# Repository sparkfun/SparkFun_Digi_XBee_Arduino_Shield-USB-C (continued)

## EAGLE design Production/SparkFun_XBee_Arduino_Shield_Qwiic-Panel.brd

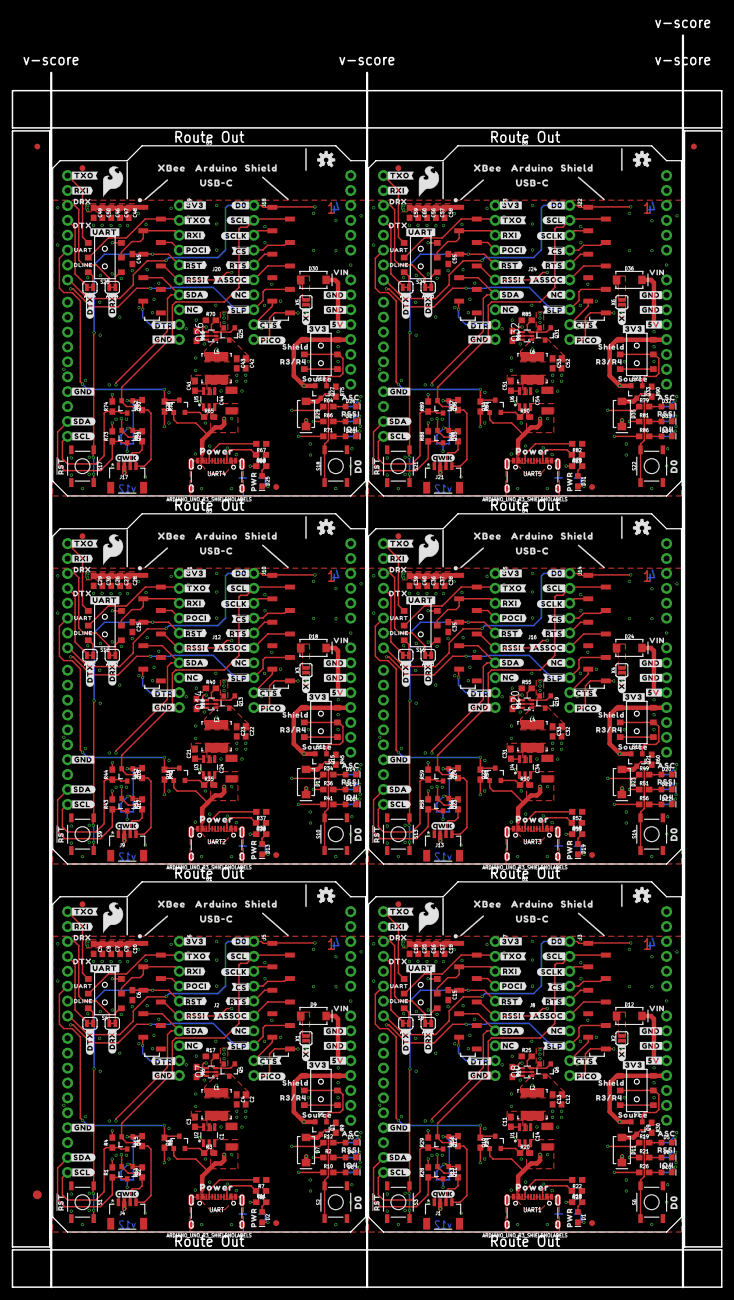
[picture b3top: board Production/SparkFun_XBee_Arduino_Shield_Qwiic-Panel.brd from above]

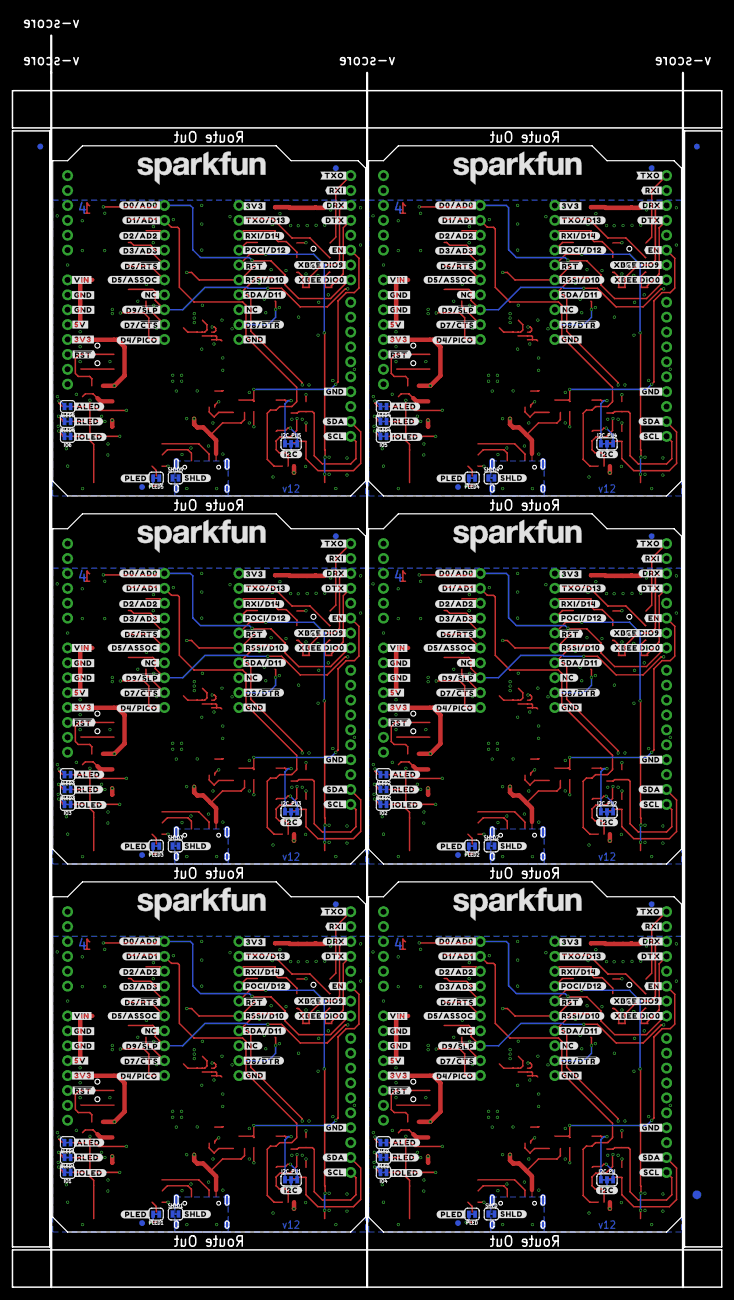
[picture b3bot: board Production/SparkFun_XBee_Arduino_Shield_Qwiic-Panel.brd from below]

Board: 4 copper layers, 120.8 x 217.2 mm, 972 parts (309 on the bottom side), 312 nets.

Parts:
ALED, ALED1, ALED2, ALED3, ALED4, ALED5: JUMPER-SMT_2_NC_TRACE_SILK; SMT-JUMPER_2_NC_TRACE_SILK
ARX, ARX1, ARX2, ARX3, ARX4, ARX5: JUMPER-SMT_2_NC_TRACE_SILK; SMT-JUMPER_2_NC_TRACE_SILK
ATX, ATX1, ATX2, ATX3, ATX4, ATX5: JUMPER-SMT_2_NC_TRACE_SILK; SMT-JUMPER_2_NC_TRACE_SILK
B1, B2, B3, B4, B5, B6: ARDUINO_UNO_R3_SHIELDNOLABELS; UNO_R3_SHIELD_NOLABELS
C1, C14, C24, C34, C44, C54: 10uF; 1210
C2, C4, C12, C13, C22, C23, C32, C33, C42, C43, C52, C53: 22uF; 0603
C3, C9, C11, C17, C21, C27, C31, C37, C41, C47, C51, C57: 0.1uF; 0603
C5, C19, C29, C39, C49, C59: 47pF; 0603
C6, C7, C15, C16, C25, C26, C35, C36, C45, C46, C55, C56: 10nF; 0603
C8, C20, C30, C40, C50, C60: 10pF; 0603
C10, C18, C28, C38, C48, C58: 10uF; 0603
D1, D2, D13, D19, D25, D31: RED; LED-0603
D3, D5, D14, D20, D26, D32: BLUE; LED-0603
D4, D8, D15, D21, D27, D33: Yellow; LED-0603
D6, D10, D16, D22, D28, D34: GREEN; LED-0603
D7, D9, D11, D12, D17, D18, D23, D24, D29, D30, D35, D36: 3A/40V/500mV; SMA-DIODE
E$1, E$2, E$3, E$4: FIDUCIAL-1X2
E$5, E$6: FIDUCIAL-1.5X3
FD1, FD2, FD3, FD4, FD5, FD6, FD7, FD8, FD9, FD10, FD11, FD12, FD13, FD14, FD15, FD16, FD17, FD18, FD19, FD20, FD21, FD22, FD23, FD24: FIDUCIAL1X2; FIDUCIAL-1X2
I2C_PU, I2C_PU1, I2C_PU2, I2C_PU3, I2C_PU4, I2C_PU5: JUMPER-SMT_3_2-NC_TRACE_SILK; SMT-JUMPER_3_2-NC_TRACE_SILK
IO1, IO2, IO3, IO4, IO5, IO6: JUMPER-SMT_2_NC_TRACE_SILK; SMT-JUMPER_2_NC_TRACE_SILK
J1, J4, J9, J13, J17, J21: QWIIC_RIGHT_ANGLE; JST04_1MM_RA
J2, J8, J12, J16, J20, J24: XBEE3-SMD
J3, J5, J6, J7, J10, J11, J14, J15, J18, J19, J22, J23: 1X10_NO_SILK
L1, L2, L3, L4, L5, L6: 3.9UH; INDUCTOR_3.9UH
LOGO1, LOGO6, LOGO9, LOGO12, LOGO15, LOGO18: SFE_LOGO_NAMEBLANK; BLANK
LOGO2, LOGO4, LOGO7, LOGO10, LOGO13, LOGO16: OSHW-LOGOS; OSHW-LOGO-S
LOGO3, LOGO5, LOGO8, LOGO11, LOGO14, LOGO17: QWIIC_LOGO_4MM; QWIIC_4MM
PLED, PLED1, PLED2, PLED3, PLED4, PLED5: JUMPER-SMT_2_NC_TRACE_SILK; SMT-JUMPER_2_NC_TRACE_SILK
Q1, Q2, Q4, Q10, Q11, Q12, Q16, Q17, Q18, Q22, Q23, Q24, Q28, Q29, Q30, Q34, Q35, Q36: 220mA/50V/3.5Ω; SOT23-3
Q3, Q9, Q15, Q21, Q27, Q33: 3.1A/30V/105mΩ; SOT23-3
Q5, Q6, Q13, Q19, Q25, Q31: 20V/4.2A/52mΩ/1.4W; SOT23-3
Q7, Q8, Q14, Q20, Q26, Q32: SOT363_PHILIPS
R1, R2, R4, R12, R13, R14, R15, R16, R19, R21, R28, R29, R31, R32, R34, R36, R43, R44, R46, R47, R49, R51, R58, R59, R61, R62, R64, R66, R73, R74, R76, R77, R79, R81, R88, R89: 2.2k; 0603
R3, R6, R9, R20, R24, R30, R35, R39, R45, R50, R54, R60, R65, R69, R75, R80, R84, R90: 100k; 0603
R5, R27, R42, R57, R72, R87: 10k; 0603
R7, R8, R22, R23, R37, R38, R52, R53, R67, R68, R82, R83: 5.1k; 0603
R10, R26, R41, R56, R71, R86: 330; 0603
R11, R18, R33, R48, R63, R78: 4.7k; 0603
R17, R25, R40, R55, R70, R85: 1M; 0603
RLED, RLED1, RLED2, RLED3, RLED4, RLED5: JUMPER-SMT_2_NC_TRACE_SILK; SMT-JUMPER_2_NC_TRACE_SILK
S1, S2, S3, S6, S9, S10, S13, S14, S17, S18, S21, S22: TACTILE_SWITCH_SMD_5.2MM
S4, S5, S7, S8, S11, S12, S15, S16, S19, S20, S23, S24: SWITCH_DPDT_SMD_AYZ0202
SHLD, SHLD1, SHLD2, SHLD3, SHLD4, SHLD5: JUMPER-SMT_2_NC_TRACE_SILK; SMT-JUMPER_2_NC_TRACE_SILK
U1, U2, U3, U4, U5, U6: AP63203; SOT23-6
U$1, U$146, U$242, U$338, U$434, U$530: RSSI31
U$2, U$147, U$243, U$339, U$435, U$531: PWR29
U$3, U$56, U$123, U$136, U$219, U$232, U$315, U$328, U$411, U$424, U$507, U$520: #SDA#10
U$4, U$130, U$226, U$322, U$418, U$514: #SHLD#36
U$5, U$9, U$131, U$135, U$227, U$231, U$323, U$327, U$419, U$423, U$515, U$519: #NC#1
U$6, U$103, U$199, U$295, U$391, U$487: #D3#AD3#23
U$7, U$10, U$132, U$133, U$228, U$229, U$324, U$325, U$420, U$421, U$516, U$517: #NC#3
U$8, U$155, U$251, U$347, U$443, U$539: ##DTR##27
U$11, U$101, U$197, U$293, U$389, U$485: #D1#AD1#8
U$12, U$156, U$252, U$348, U$444, U$540: ##CTS##28
U$13, U$109, U$205, U$301, U$397, U$493: #D8##DTR##27
U$14, U$110, U$206, U$302, U$398, U$494: #RSSI#D10#17
U$15, U$111, U$207, U$303, U$399, U$495: #SDA#D11#9
U$16, U$112, U$208, U$304, U$400, U$496: ##RST##15
U$17, U$113, U$209, U$305, U$401, U$497: #POCI#D12#24
U$18, U$114, U$210, U$306, U$402, U$498: #RXI#D14#15
U$19, U$102, U$198, U$294, U$390, U$486: #D2#AD2#19
U$20, U$104, U$200, U$296, U$392, U$488: #D6##RTS##25
U$21, U$32, U$118, U$139, U$214, U$235, U$310, U$331, U$406, U$427, U$502, U$523: #TXO#8
U$22, U$115, U$211, U$307, U$403, U$499: #TXO#D13#13
U$23, U$162, U$258, U$354, U$450, U$546: VIN5
U$24, U$137, U$233, U$329, U$425, U$521: #SCL#7
U$25, U$29, U$41, U$50, U$53, U$63, U$76, U$82, U$134, U$138, U$142, U$148, U$157, U$165, U$166, U$170, U$230, U$234, U$238, U$244, U$253, U$261, U$262, U$266, U$326, U$330, U$334, U$340, U$349, U$357, U$358, U$362, U$422, U$426, U$430, U$436, U$445, U$453, U$454, U$458, U$518, U$522, U$526, U$532, U$541, U$549, U$550, U$554: #GND#0
U$26, U$97, U$193, U$289, U$385, U$481: #I2C#33
U$27, U$33, U$119, U$140, U$215, U$236, U$311, U$332, U$407, U$428, U$503, U$524: #RXI#7
U$28, U$177, U$273, U$369, U$465, U$561: DRX52
U$30, U$99, U$195, U$291, U$387, U$483: #RST#30
U$31, U$163, U$259, U$355, U$451, U$547: #PICO#27
U$34, U$178, U$274, U$370, U$466, U$562: DTX53
U$35, U$105, U$201, U$297, U$393, U$489: #D5#ASSOC#25
U$36, U$106, U$202, U$298, U$394, U$490: #D9##SLP##28
U$37, U$107, U$203, U$299, U$395, U$491: #D7##CTS##26
U$38, U$108, U$204, U$300, U$396, U$492: #D4#PICO#25
U$39, U$66, U$154, U$167, U$250, U$263, U$346, U$359, U$442, U$455, U$538, U$551: #5V#5
U$40, U$98, U$194, U$290, U$386, U$482: D03
U$42, U$179, U$275, U$371, U$467, U$563: DLINE45
U$43, U$164, U$260, U$356, U$452, U$548: #X1#10
U$44, U$47, U$77, U$84, U$141, U$149, U$158, U$172, U$237, U$245, U$254, U$268, U$333, U$341, U$350, U$364, U$429, U$437, U$446, U$460, U$525, U$533, U$542, U$556: #3V3#1
U$45, U$120, U$216, U$312, U$408, U$504: #POCI#32
U$46, U$190, U$286, U$382, U$478, U$574: SHIELD55
U$48, U$180, U$276, U$372, U$468, U$564: UART44
U$49, U$116, U$212, U$308, U$404, U$500: #ALED#21
U$51, U$117, U$213, U$309, U$405, U$501: #RLED#22
U$52, U$159, U$255, U$351, U$447, U$543: #PLED#20
U$54, U$87, U$121, U$173, U$217, U$269, U$313, U$365, U$409, U$461, U$505, U$557: ##RST##13
U$55, U$122, U$218, U$314, U$410, U$506: #RSSI#16
U$57, U$124, U$220, U$316, U$412, U$508: #ASSOC#28
U$58, U$125, U$221, U$317, U$413, U$509: ##RTS##14
U$59, U$126, U$222, U$318, U$414, U$510: ##CS##26
U$60, U$127, U$223, U$319, U$415, U$511: #SCLK#33
U$61, U$100, U$196, U$292, U$388, U$484: SFE_LOGO_FLAME_.2
U$62, U$143, U$239, U$335, U$431, U$527: SFE_LOGO_NAME_.2
U$64, U$128, U$224, U$320, U$416, U$512: #SCL#9
U$65, U$129, U$225, U$321, U$417, U$513: #D0#3
U$67, U$168, U$264, U$360, U$456, U$552: #SDA#9
U$68, U$144, U$240, U$336, U$432, U$528: ##SLP##28
U$69, U$191, U$287, U$383, U$479, U$575: R3#R455
U$70, U$169, U$265, U$361, U$457, U$553: #SCL#13
U$71, U$86, U$181, U$185, U$277, U$281, U$373, U$377, U$469, U$473, U$565, U$569: #DRX#56
U$72, U$89, U$182, U$186, U$278, U$282, U$374, U$378, U$470, U$474, U$566, U$570: #DTX#57
U$73, U$183, U$279, U$375, U$471, U$567: #TXO#61
U$74, U$145, U$241, U$337, U$433, U$529: ASC32
U$75, U$176, U$272, U$368, U$464, U$560: POWER49
U$78, U$150, U$246, U$342, U$438, U$534: #D0#AD0#18
U$79, U$151, U$247, U$343, U$439, U$535: ARDUINO1345
U$80, U$152, U$248, U$344, U$440, U$536: XBEE340
U$81, U$153, U$249, U$345, U$441, U$537: SHIELD1346
U$83, U$171, U$267, U$363, U$459, U$555: #EN#15
U$85, U$184, U$280, U$376, U$472, U$568: #RXI#60
U$88, U$174, U$270, U$366, U$462, U$558: #VIN#4
U$90, U$187, U$283, U$379, U$475, U$571: #XBEE_DIO0#62
U$91, U$175, U$271, U$367, U$463, U$559: #UART#4048234
U$92, U$188, U$284, U$380, U$476, U$572: #XBEE_DIO9#62
U$93, U$160, U$256, U$352, U$448, U$544: #IOLED#5
U$94, U$161, U$257, U$353, U$449, U$545: IO49
U$95, U$189, U$285, U$381, U$477, U$573: SOURCE54
U$96, U$192, U$288, U$384, U$480, U$576: USB#C58
UART, UART1, UART2, UART3, UART4, UART5: USB Female Type C Connector; USB-C-16P-4LAYER-ISOLATED
X1, X2, X3, X4, X5, X6: JUMPER-SMT_2_NO_SILK; SMT-JUMPER_2_NO_SILK

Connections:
3.3V: C5.1, C7.1, C8.1, C9.1, C10.1, D7.C, I2C_PU.2, J2.1, J4.2, J6.1, Q5.2, Q7.4, R11.1
3.3V1: C16.1, C17.1, C18.1, C19.1, C20.1, D11.C, I2C_PU1.2, J1.2, J7.1, J8.1, Q6.2, Q8.4, R18.1
3.3V2: C26.1, C27.1, C28.1, C29.1, C30.1, D17.C, I2C_PU2.2, J9.2, J11.1, J12.1, Q13.2, Q14.4, R33.1
3.3V3: C36.1, C37.1, C38.1, C39.1, C40.1, D23.C, I2C_PU3.2, J13.2, J15.1, J16.1, Q19.2, Q20.4, R48.1
3.3V4: C46.1, C47.1, C48.1, C49.1, C50.1, D29.C, I2C_PU4.2, J17.2, J19.1, J20.1, Q25.2, Q26.4, R63.1
3.3V5: C56.1, C57.1, C58.1, C59.1, C60.1, D35.C, I2C_PU5.2, J21.2, J23.1, J24.1, Q31.2, Q32.4, R78.1
3.3V_R1: B2.3.3V, Q9.2, R27.2, R28.2, R29.2, S7.3, S7.6
3.3V_R2: B3.3.3V, Q15.2, R42.2, R43.2, R44.2, S11.3, S11.6
3.3V_R3: B1.3.3V, Q3.2, R1.2, R4.2, R5.2, S5.3, S5.6
3.3V_R4: B4.3.3V, Q21.2, R57.2, R58.2, R59.2, S15.3, S15.6
3.3V_R5: B5.3.3V, Q27.2, R72.2, R73.2, R74.2, S19.3, S19.6
3.3V_R6: B6.3.3V, Q33.2, R87.2, R88.2, R89.2, S23.3, S23.6
3.3V_VREG: C2.1, C4.1, L1.P$2, Q5.3, Q7.1, U2.1
3.3V_VREG1: C12.1, C13.1, L2.P$2, Q6.3, Q8.1, U1.1
3.3V_VREG2: C22.1, C23.1, L3.P$2, Q13.3, Q14.1, U3.1
3.3V_VREG3: C32.1, C33.1, L4.P$2, Q19.3, Q20.1, U4.1
3.3V_VREG4: C42.1, C43.1, L5.P$2, Q25.3, Q26.1, U5.1
3.3V_VREG5: C52.1, C53.1, L6.P$2, Q31.3, Q32.1, U6.1
5V: B1.5V, D9.C
5V1: B2.5V, D12.C
5V2: B3.5V, D18.C
5V3: B4.5V, D24.C
5V4: B5.5V, D30.C
5V5: B6.5V, D36.C
!RESET!: C6.1, J2.5, J6.5, S1.1, S1.2
!RESET!1: C15.1, J7.5, J8.5, S3.1, S3.2
!RESET!2: C25.1, J11.5, J12.5, S9.1, S9.2
!RESET!3: C35.1, J15.5, J16.5, S13.1, S13.2
!RESET!4: C45.1, J19.5, J20.5, S17.1, S17.2
!RESET!5: C55.1, J23.5, J24.5, S21.1, S21.2
D0: B1.D7, J2.20, J5.1, S2.1, S2.2
D1: B2.D7, J3.1, J8.20, S6.1, S6.2
D1/SCL: J2.19, J4.4, J5.2, Q4.2, R15.1
D1/SCL1: J1.4, J3.2, J8.19, Q12.2, R16.1
D1/SCL2: J9.4, J10.2, J12.19, Q18.2, R32.1
D1/SCL3: J13.4, J14.2, J16.19, Q24.2, R47.1
D1/SCL4: J17.4, J18.2, J20.19, Q30.2, R62.1
D1/SCL5: J21.4, J22.2, J24.19, Q36.2, R77.1
D2: B3.D7, J10.1, J12.20, S10.1, S10.2
D2/SPI_CLK: J2.18, J5.3
D2/SPI_CLK1: J3.3, J8.18
D2/SPI_CLK2: J10.3, J12.18
D2/SPI_CLK3: J14.3, J16.18
D2/SPI_CLK4: J18.3, J20.18
D2/SPI_CLK5: J22.3, J24.18
D3: B4.D7, J14.1, J16.20, S14.1, S14.2
D3/SPI_!CS!: J2.17, J5.4
D3/SPI_!CS!1: J3.4, J8.17
D3/SPI_!CS!2: J10.4, J12.17
D3/SPI_!CS!3: J14.4, J16.17
D3/SPI_!CS!4: J18.4, J20.17
D3/SPI_!CS!5: J22.4, J24.17
D4: B5.D7, J18.1, J20.20, S18.1, S18.2
D4/SPI_PICO: J2.11, J5.10, R10.1
D4/SPI_PICO1: J3.10, J8.11, R26.1
D4/SPI_PICO2: J10.10, J12.11, R41.1
D4/SPI_PICO3: J14.10, J16.11, R56.1
D4/SPI_PICO4: J18.10, J20.11, R71.1
D4/SPI_PICO5: J22.10, J24.11, R86.1
D5: B6.D7, J22.1, J24.20, S22.1, S22.2
D5/ASSOCIATE: J2.15, J5.6, R12.1
D5/ASSOCIATE1: J3.6, J8.15, R19.1
D5/ASSOCIATE2: J10.6, J12.15, R34.1
D5/ASSOCIATE3: J14.6, J16.15, R49.1
D5/ASSOCIATE4: J18.6, J20.15, R64.1
D5/ASSOCIATE5: J22.6, J24.15, R79.1
D6/!RTS!: J2.16, J5.5
D6/!RTS!1: J3.5, J8.16
D6/!RTS!2: J10.5, J12.16
D6/!RTS!3: J14.5, J16.16
D6/!RTS!4: J18.5, J20.16
D6/!RTS!5: J22.5, J24.16
D7/!CTS!: J2.12, J5.9
D7/!CTS!1: J3.9, J8.12
D7/!CTS!2: J10.9, J12.12
D7/!CTS!3: J14.9, J16.12
D7/!CTS!4: J18.9, J20.12
D7/!CTS!5: J22.9, J24.12
D8/!DTR!: J2.9, J6.9
D8/!DTR!1: J7.9, J8.9
D8/!DTR!2: J11.9, J12.9
D8/!DTR!3: J15.9, J16.9
D8/!DTR!4: J19.9, J20.9
D8/!DTR!5: J23.9, J24.9
D9/!SLEEP!: B1.D6, J2.13, J5.8
D9/!SLEEP!1: B2.D6, J3.8, J8.13
D9/!SLEEP!2: B3.D6, J10.8, J12.13
D9/!SLEEP!3: B4.D6, J14.8, J16.13
D9/!SLEEP!4: B5.D6, J18.8, J20.13
D9/!SLEEP!5: B6.D6, J22.8, J24.13
D10/RSSI_PWM: J2.6, J6.6, R2.1
D10/RSSI_PWM1: J7.6, J8.6, R21.1
D10/RSSI_PWM2: J11.6, J12.6, R36.1
D10/RSSI_PWM3: J15.6, J16.6, R51.1
D10/RSSI_PWM4: J19.6, J20.6, R66.1
D10/RSSI_PWM5: J23.6, J24.6, R81.1
D11/SDA: J2.7, J4.3, J6.7, Q2.2, R14.1
D11/SDA1: J1.3, J7.7, J8.7, Q11.2, R13.1
D11/SDA2: J9.3, J11.7, J12.7, Q17.2, R31.1
D11/SDA3: J13.3, J15.7, J16.7, Q23.2, R46.1
D11/SDA4: J17.3, J19.7, J20.7, Q29.2, R61.1
D11/SDA5: J21.3, J23.7, J24.7, Q35.2, R76.1
D12/SPI_POCI: J2.4, J6.4
D12/SPI_POCI1: J7.4, J8.4
D12/SPI_POCI2: J11.4, J12.4
D12/SPI_POCI3: J15.4, J16.4
D12/SPI_POCI4: J19.4, J20.4
D12/SPI_POCI5: J23.4, J24.4
D13/TXO: J2.2, J6.2, S4.2
D13/TXO1: J7.2, J8.2, S8.2
D13/TXO2: J11.2, J12.2, S12.2
D13/TXO3: J15.2, J16.2, S16.2
D13/TXO4: J19.2, J20.2, S20.2
D13/TXO5: J23.2, J24.2, S24.2
D13/TXO-R1: B2.RX, S8.3
D13/TXO-R2: B3.RX, S12.3
D13/TXO-R3: B1.RX, S4.3
D13/TXO-R4: B4.RX, S16.3
D13/TXO-R5: B5.RX, S20.3
D13/TXO-R6: B6.RX, S24.3
D14/RXI: J2.3, J6.3, S4.5
D14/RXI1: J7.3, J8.3, S8.5
D14/RXI2: J11.3, J12.3, S12.5
D14/RXI3: J15.3, J16.3, S16.5
D14/RXI4: J19.3, J20.3, S20.5
D14/RXI5: J23.3, J24.3, S24.5
D14/RXI-R1: B2.TX, S8.6
D14/RXI-R2: B3.TX, S12.6
D14/RXI-R3: B1.TX, S4.6
D14/RXI-R4: B4.TX, S16.6
D14/RXI-R5: B5.TX, S20.6
D14/RXI-R6: B6.TX, S24.6
D_RX: ARX.2, B1.D2
D_RX1: ARX1.2, B2.D2
D_RX2: ARX2.2, B3.D2
D_RX3: ARX3.2, B4.D2
D_RX4: ARX4.2, B5.D2
D_RX5: ARX5.2, B6.D2
D_RX_JUMP: ARX.1, S4.4
D_RX_JUMP1: ARX1.1, S8.4
D_RX_JUMP2: ARX2.1, S12.4
D_RX_JUMP3: ARX3.1, S16.4
D_RX_JUMP4: ARX4.1, S20.4
D_RX_JUMP5: ARX5.1, S24.4
D_TX: ATX.2, B1.D3
D_TX1: ATX1.2, B2.D3
D_TX2: ATX2.2, B3.D3
D_TX3: ATX3.2, B4.D3
D_TX4: ATX4.2, B5.D3
D_TX5: ATX5.2, B6.D3
D_TX_JUMP: ATX.1, S4.1
D_TX_JUMP1: ATX1.1, S8.1
D_TX_JUMP2: ATX2.1, S12.1
D_TX_JUMP3: ATX3.1, S16.1
D_TX_JUMP4: ATX4.1, S20.1
D_TX_JUMP5: ATX5.1, S24.1
EN: Q1.2, R3.1, U2.2
EN1: Q10.2, R20.1, U1.2
EN2: Q16.2, R35.1, U3.2
EN3: Q22.2, R50.1, U4.2
EN4: Q28.2, R65.1, U5.2
EN5: Q34.2, R80.1, U6.2
EN-TRANS: B1.D5, Q1.3, R5.1
EN-TRANS1: B2.D5, Q10.3, R27.1
EN-TRANS2: B3.D5, Q16.3, R42.1
EN-TRANS3: B4.D5, Q22.3, R57.1
EN-TRANS4: B5.D5, Q28.3, R72.1
EN-TRANS5: B6.D5, Q34.3, R87.1
GND: ALED.1, B1.GND@0, B1.GND@1, B1.GND@2, C1.2, C2.2, C4.2, C5.2, C6.2, C7.2, C8.2, C9.2, C10.2, IO4.1, J2.10, J4.1, J6.10, PLED.1, R6.1, R7.1, R8.1, R9.1, R17.1, RLED.1, S1.3, S1.4, S2.3, S2.4, S5.1, S5.4, SHLD.1, U2.4, UART.GND, UART.GND2
GND1: ALED1.1, B2.GND@0, B2.GND@1, B2.GND@2, C12.2, C13.2, C14.2, C15.2, C16.2, C17.2, C18.2, C19.2, C20.2, IO1.1, J1.1, J7.10, J8.10, PLED1.1, R22.1, R23.1, R24.1, R25.1, R30.1, RLED1.1, S3.3, S3.4, S6.3, S6.4, S7.1, S7.4, SHLD1.1, U1.4, UART1.GND, UART1.GND2
GND2: ALED2.1, B3.GND@0, B3.GND@1, B3.GND@2, C22.2, C23.2, C24.2, C25.2, C26.2, C27.2, C28.2, C29.2, C30.2, IO2.1, J9.1, J11.10, J12.10, PLED2.1, R37.1, R38.1, R39.1, R40.1, R45.1, RLED2.1, S9.3, S9.4, S10.3, S10.4, S11.1, S11.4, SHLD2.1, U3.4, UART2.GND, UART2.GND2
GND3: ALED3.1, B4.GND@0, B4.GND@1, B4.GND@2, C32.2, C33.2, C34.2, C35.2, C36.2, C37.2, C38.2, C39.2, C40.2, IO3.1, J13.1, J15.10, J16.10, PLED3.1, R52.1, R53.1, R54.1, R55.1, R60.1, RLED3.1, S13.3, S13.4, S14.3, S14.4, S15.1, S15.4, SHLD3.1, U4.4, UART3.GND, UART3.GND2
GND4: ALED4.1, B5.GND@0, B5.GND@1, B5.GND@2, C42.2, C43.2, C44.2, C45.2, C46.2, C47.2, C48.2, C49.2, C50.2, IO5.1, J17.1, J19.10, J20.10, PLED4.1, R67.1, R68.1, R69.1, R70.1, R75.1, RLED4.1, S17.3, S17.4, S18.3, S18.4, S19.1, S19.4, SHLD4.1, U5.4, UART4.GND, UART4.GND2
GND5: ALED5.1, B6.GND@0, B6.GND@1, B6.GND@2, C52.2, C53.2, C54.2, C55.2, C56.2, C57.2, C58.2, C59.2, C60.2, IO6.1, J21.1, J23.10, J24.10, PLED5.1, R82.1, R83.1, R84.1, R85.1, R90.1, RLED5.1, S21.3, S21.4, S22.3, S22.4, S23.1, S23.4, SHLD5.1, U6.4, UART5.GND, UART5.GND2
unnamed: C3.1, U2.6
unnamed: D4.A, R2.2
unnamed: D4.C, RLED.2
unnamed: D6.A, R10.2
unnamed: R8.2, UART.B5
unnamed: R7.2, UART.A5
unnamed: D2.A, R11.2
unnamed: C3.2, L1.P$1, U2.5
unnamed: D9.A, X1.2
unnamed: I2C_PU.1, Q4.1, R15.2
unnamed: I2C_PU.3, Q2.1, R14.2
unnamed: D3.A, R12.2
unnamed: I2C_PU1.3, Q11.1, R13.2
unnamed: D1.A, R18.2
unnamed: D5.A, R19.2
unnamed: D7.A, Q3.3, R9.2
unnamed: D6.C, IO4.2
unnamed: ALED1.2, D5.C
unnamed: Q7.2, Q7.5, Q7.6, R6.2
unnamed: Q5.1, Q7.3, R17.2
unnamed: ALED.2, D3.C
unnamed: D1.C, PLED1.2
unnamed: D2.C, PLED.2
unnamed: C11.1, U1.6
unnamed: C11.2, L2.P$1, U1.5
unnamed: D8.A, R21.2
unnamed: Q3.1, S5.2, S5.5
unnamed: D8.C, RLED1.2
unnamed: R23.2, UART1.B5
unnamed: R22.2, UART1.A5
unnamed: Q8.2, Q8.5, Q8.6, R24.2
unnamed: Q6.1, Q8.3, R25.2
unnamed: D10.A, R26.2
unnamed: D10.C, IO1.2
unnamed: Q9.1, S7.2, S7.5
unnamed: D11.A, Q9.3, R30.2
unnamed: D12.A, X2.2
unnamed: I2C_PU1.1, Q12.1, R16.2
unnamed: I2C_PU2.3, Q17.1, R31.2
unnamed: D13.A, R33.2
unnamed: D14.A, R34.2
unnamed: ALED2.2, D14.C
unnamed: D13.C, PLED2.2
unnamed: C21.1, U3.6
unnamed: C21.2, L3.P$1, U3.5
unnamed: D15.A, R36.2
unnamed: D15.C, RLED2.2
unnamed: R38.2, UART2.B5
unnamed: R37.2, UART2.A5
unnamed: Q14.2, Q14.5, Q14.6, R39.2
unnamed: Q13.1, Q14.3, R40.2
unnamed: D16.A, R41.2
unnamed: D16.C, IO2.2
unnamed: Q15.1, S11.2, S11.5
unnamed: D17.A, Q15.3, R45.2
unnamed: D18.A, X3.2
unnamed: I2C_PU2.1, Q18.1, R32.2
unnamed: I2C_PU3.3, Q23.1, R46.2
unnamed: D19.A, R48.2
unnamed: D20.A, R49.2
unnamed: ALED3.2, D20.C
unnamed: D19.C, PLED3.2
unnamed: C31.1, U4.6
unnamed: C31.2, L4.P$1, U4.5
unnamed: D21.A, R51.2
unnamed: D21.C, RLED3.2
unnamed: R53.2, UART3.B5
unnamed: R52.2, UART3.A5
unnamed: Q20.2, Q20.5, Q20.6, R54.2
unnamed: Q19.1, Q20.3, R55.2
unnamed: D22.A, R56.2
unnamed: D22.C, IO3.2
unnamed: Q21.1, S15.2, S15.5
unnamed: D23.A, Q21.3, R60.2
unnamed: D24.A, X4.2
unnamed: I2C_PU3.1, Q24.1, R47.2
unnamed: I2C_PU4.3, Q29.1, R61.2
unnamed: D25.A, R63.2
unnamed: D26.A, R64.2
unnamed: ALED4.2, D26.C
unnamed: D25.C, PLED4.2
unnamed: C41.1, U5.6
unnamed: C41.2, L5.P$1, U5.5
unnamed: D27.A, R66.2
unnamed: D27.C, RLED4.2
unnamed: R68.2, UART4.B5
unnamed: R67.2, UART4.A5
unnamed: Q26.2, Q26.5, Q26.6, R69.2
unnamed: Q25.1, Q26.3, R70.2
unnamed: D28.A, R71.2
unnamed: D28.C, IO5.2
unnamed: Q27.1, S19.2, S19.5
unnamed: D29.A, Q27.3, R75.2
unnamed: D30.A, X5.2
unnamed: I2C_PU4.1, Q30.1, R62.2
unnamed: I2C_PU5.3, Q35.1, R76.2
unnamed: D31.A, R78.2
unnamed: D32.A, R79.2
unnamed: ALED5.2, D32.C
unnamed: D31.C, PLED5.2
unnamed: C51.1, U6.6
unnamed: C51.2, L6.P$1, U6.5
unnamed: D33.A, R81.2
unnamed: D33.C, RLED5.2
unnamed: R83.2, UART5.B5
unnamed: R82.2, UART5.A5
unnamed: Q32.2, Q32.5, Q32.6, R84.2
unnamed: Q31.1, Q32.3, R85.2
unnamed: D34.A, R86.2
unnamed: D34.C, IO6.2
unnamed: Q33.1, S23.2, S23.5
unnamed: D35.A, Q33.3, R90.2
unnamed: D36.A, X6.2
unnamed: I2C_PU5.1, Q36.1, R77.2
R3_D1/SCL: B1.SCL, Q4.3, R4.1
R3_D1/SCL1: B2.SCL, Q12.3, R29.1
R3_D1/SCL2: B3.SCL, Q18.3, R44.1
R3_D1/SCL3: B4.SCL, Q24.3, R59.1
R3_D1/SCL4: B5.SCL, Q30.3, R74.1
R3_D1/SCL5: B6.SCL, Q36.3, R89.1
R3_D11/SDA: B1.SDA, Q2.3, R1.1
R3_D11/SDA1: B2.SDA, Q11.3, R28.1
R3_D11/SDA2: B3.SDA, Q17.3, R43.1
R3_D11/SDA3: B4.SDA, Q23.3, R58.1
R3_D11/SDA4: B5.SDA, Q29.3, R73.1
R3_D11/SDA5: B6.SDA, Q35.3, R88.1
SHLD: SHLD.2, UART.SHLD1, UART.SHLD2, UART.SHLD3, UART.SHLD4, UART.SHLD5, UART.SHLD6, UART.SHLD7, UART.SHLD8
SHLD1: SHLD1.2, UART1.SHLD1, UART1.SHLD2, UART1.SHLD3, UART1.SHLD4, UART1.SHLD5, UART1.SHLD6, UART1.SHLD7, UART1.SHLD8
SHLD2: SHLD2.2, UART2.SHLD1, UART2.SHLD2, UART2.SHLD3, UART2.SHLD4, UART2.SHLD5, UART2.SHLD6, UART2.SHLD7, UART2.SHLD8
SHLD3: SHLD3.2, UART3.SHLD1, UART3.SHLD2, UART3.SHLD3, UART3.SHLD4, UART3.SHLD5, UART3.SHLD6, UART3.SHLD7, UART3.SHLD8
SHLD4: SHLD4.2, UART4.SHLD1, UART4.SHLD2, UART4.SHLD3, UART4.SHLD4, UART4.SHLD5, UART4.SHLD6, UART4.SHLD7, UART4.SHLD8
SHLD5: SHLD5.2, UART5.SHLD1, UART5.SHLD2, UART5.SHLD3, UART5.SHLD4, UART5.SHLD5, UART5.SHLD6, UART5.SHLD7, UART5.SHLD8
V_USB: C1.1, Q1.1, R3.2, U2.3, UART.VBUS1, UART.VBUS2, X1.1
V_USB1: C14.1, Q10.1, R20.2, U1.3, UART1.VBUS1, UART1.VBUS2, X2.1
V_USB2: C24.1, Q16.1, R35.2, U3.3, UART2.VBUS1, UART2.VBUS2, X3.1
V_USB3: C34.1, Q22.1, R50.2, U4.3, UART3.VBUS1, UART3.VBUS2, X4.1
V_USB4: C44.1, Q28.1, R65.2, U5.3, UART4.VBUS1, UART4.VBUS2, X5.1
V_USB5: C54.1, Q34.1, R80.2, U6.3, UART5.VBUS1, UART5.VBUS2, X6.1
